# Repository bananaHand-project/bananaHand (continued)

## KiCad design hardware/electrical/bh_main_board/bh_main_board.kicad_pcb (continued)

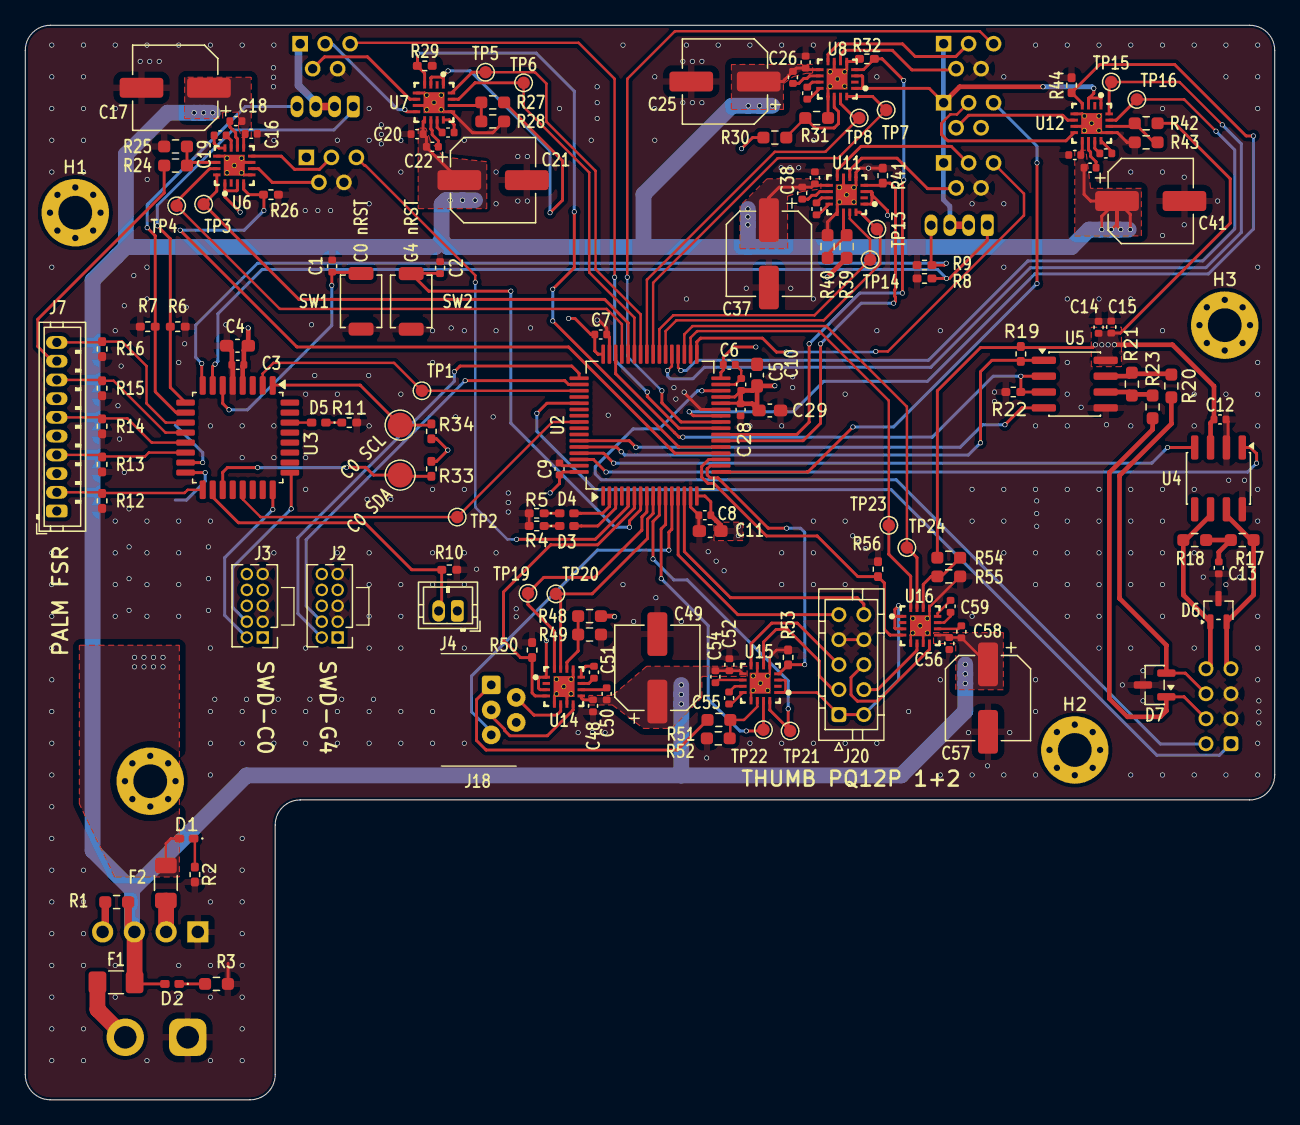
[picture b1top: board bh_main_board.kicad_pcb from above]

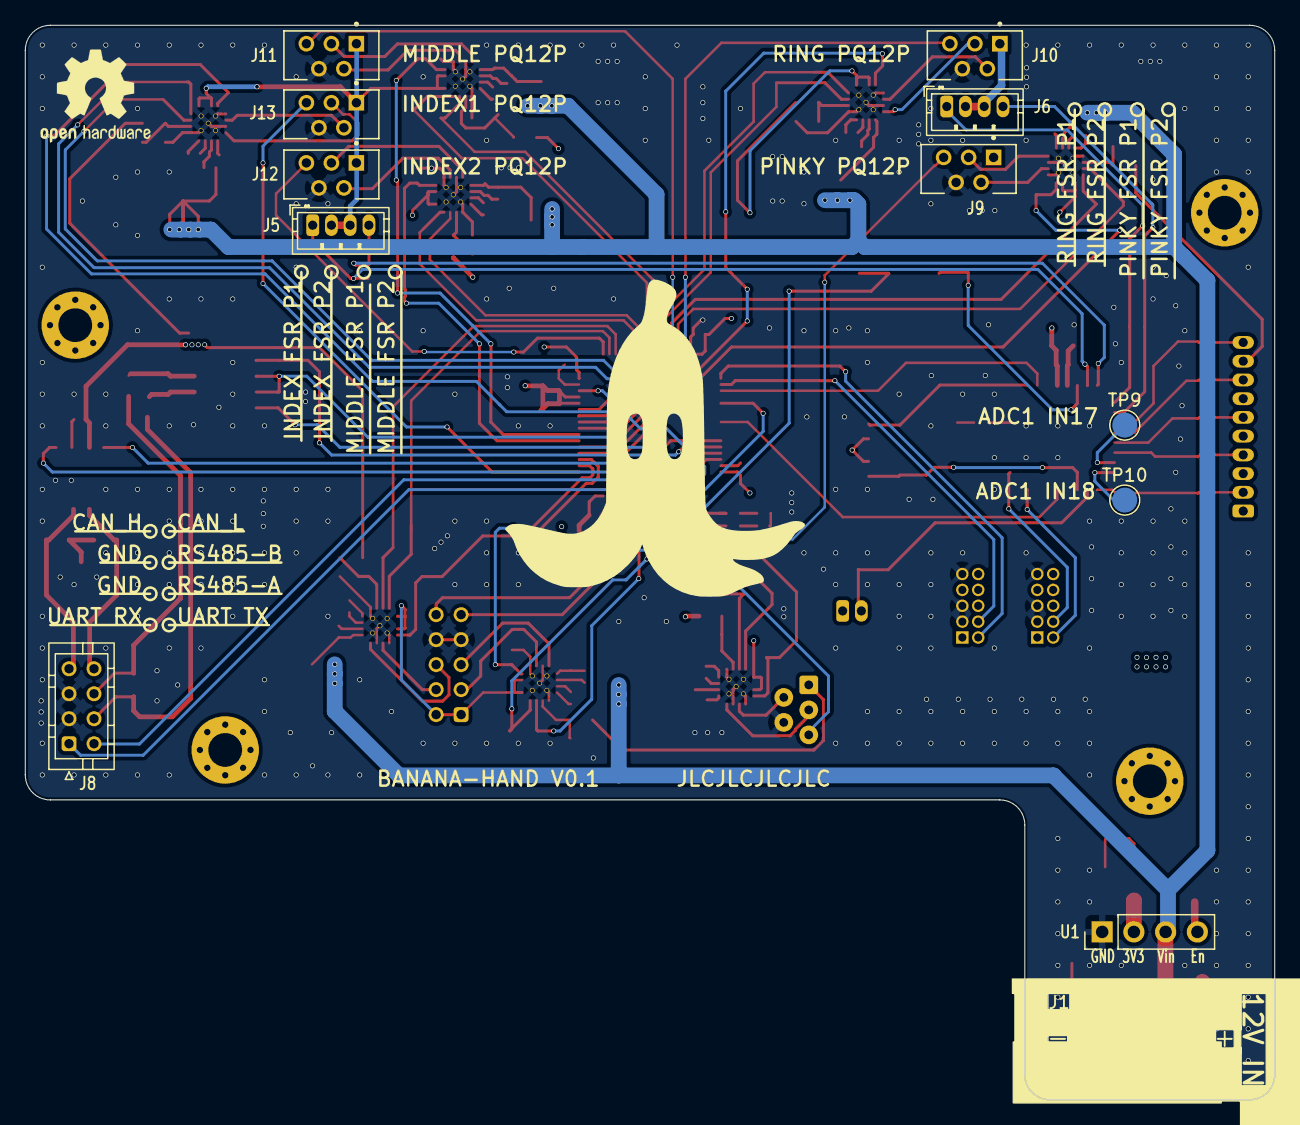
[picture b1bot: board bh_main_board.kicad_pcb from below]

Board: 4 copper layers, 100.0 x 86.0 mm, 163 parts (14 on the bottom side), 130 nets.

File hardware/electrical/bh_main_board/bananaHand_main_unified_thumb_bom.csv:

"Reference","Qty","Value","DNP","Exclude from BOM","Exclude from Board","Footprint","Datasheet","MFR #","LCSC #"
"U6,U7,U8,U11,U12,U14,U15,U16","8","DRV8876GTR","","","","bananaHand:DRV8876GTR-MFG","https://www.ti.com/lit/ds/symlink/drv8876.pdf","DRV8876RGTR","C1852100"
"J18","1","HLW5R-2C7LF","","","","bananaHand:HLW5R-2C7LF","","HLW5R-2C7LF","C5406452"
"J9,J10,J11,J12,J13","5","HLW5S-2C7LF","","","","bananaHand:HLW5S-2C7LF","","HLW5S-2C7LF","C5406437"
"ART1","1","~","","Excluded from BOM","","bananaHand:mk_banana_footprint","","",""
"U1","1","MPM3610_3V3_Buck_Brkout","","","","bananaHand:MP3610_3V3_BUCK_BREAKOUT","https://github.com/adafruit/Adafruit-MPM3610-PCB","",""
"SW1,SW2","2","SW_Push","","","","Button_Switch_SMD:SW_SPST_TS-1088-xR025","~","TS-1088R-02526","C455281"
"C1,C2,C3,C6,C7,C8,C9,C12,C14,C15,C16,C18,C20,C22,C24,C26,C36,C38,C40,C42,C48,C50,C52,C54,C56,C58","26","100nF","","","","Capacitor_SMD:C_0402_1005Metric","~"," GRM155R71H104KE14D","C77020"
"C5","1","10nF","","","","Capacitor_SMD:C_0402_1005Metric","~"," GRM155R71H103KA88D","C77019"
"C13","1","4nF7","","","","Capacitor_SMD:C_0402_1005Metric","~","GRM1555C1H472JE01D","C1518204"
"C19,C23,C27,C39,C43,C51,C55,C59","8","22nF","","","","Capacitor_SMD:C_0402_1005Metric","~"," GRM155R71H223KA12D","C77023"
"C4,C11","2","4uF7","","","","Capacitor_SMD:C_0603_1608Metric_Pad1.08x0.95mm_HandSolder","~"," GRM188R6YA475KE15D","C162274"
"C10","1","1uF","","","","Capacitor_SMD:C_0603_1608Metric_Pad1.08x0.95mm_HandSolder","~","GCM188R71E105KA64D","C85862"
"C17,C21,C25,C37,C41,C57","6","47uF","","","","Capacitor_SMD:CP_Elec_6.3x5.8","~","EEEFP1V470AP","C401754"
"C49","1","100uF","","","","Capacitor_SMD:CP_Elec_6.3x5.8","~"," EEEFT1V101AP","C128464"
"J1","1","Conn_01x02_Pin","","","","Connector_AMASS:AMASS_XT30UPB-M_1x02_P5.0mm_Vertical","~","XT30UPB-M","C428721"
"J20","1","Conn_02x05_Odd_Even","","","","Connector_JST:JST_PHD_B10B-PHDSS_2x05_P2.00mm_Vertical","~","B10B-PHDSS(LF)(SN)","C471519"
"J8","1","Conn_02x04_Top_Bottom","","","","Connector_JST:JST_PHD_B8B-PHDSS_2x04_P2.00mm_Vertical","~","B8B-PHDSS(LF)(SN)","C157975"
"J7","1","Conn_01x10","","","","Connector_JST:JST_ZH_B10B-ZR_1x10_P1.50mm_Vertical","~","B10B-ZR(LF)(SN)","C158036"
"J4","1","Conn_01x02_Pad","","","","Connector_JST:JST_ZH_B2B-ZR_1x02_P1.50mm_Vertical","~","JST B2B-ZR(LF)(SN)","C158011"
"J5,J6","2","Conn_01x04_Pin","","","","Connector_JST:JST_ZH_B4B-ZR_1x04_P1.50mm_Vertical","~","JST B4B-ZR(LF)(SN)","C157997"
"J2,J3","2","Conn_02x05_Top_Bottom","","","","Connector_PinHeader_1.27mm:PinHeader_2x05_P1.27mm_Vertical","~","ZX-PZ1.27-2-5PZZ","C7501289"
"F2","1","750mA 36V","","","","Fuse:Fuse_1206_3216Metric","https://www.lcsc.com/datasheet/C49196638.pdf"," 1206L075/36NR","C49196638"
"F1","1","1A8 33V","","","","Fuse:Fuse_1206_3216Metric_Pad1.42x1.75mm_HandSolder","https://www.lcsc.com/datasheet/C49318377.pdf","YTL 1206L100/33V","C49318377"
"D1,D2,D3,D4,D5","5","LED","","","","LED_SMD:LED_0402_1005Metric_Pad0.77x0.64mm_HandSolder","~","XL-1005UYC","C25503856"
"H1,H2,H3","3","MountingHole","","Excluded from BOM","","MountingHole:MountingHole_2.5mm_Pad_Via","~","",""
"U3","1","STM32C071K8Tx","","","","Package_QFP:LQFP-32_7x7mm_P0.8mm","https://www.st.com/resource/en/datasheet/stm32c071k8.pdf","STM32C071K8T6","C43650208"
"U2","1","STM32G474RETx","","","","Package_QFP:LQFP-64_10x10mm_P0.5mm","https://www.st.com/resource/en/datasheet/stm32g474re.pdf","STM32G474RET6","C521608"
"U4","1","SN65HVD230DR","","","","Package_SO:SOIC-8_3.9x4.9mm_P1.27mm","http://www.ti.com/lit/ds/symlink/sn65hvd230.pdf","SN65HVD230DR","C12084"
"U5","1","SN65HVD1781","","","","Package_SO:SOIC-8_3.9x4.9mm_P1.27mm","https://www.ti.com/lit/ds/symlink/sn65hvd1781.pdf","SN65HVD1781DR","C42737"
"D7","1","SM712_SOT23","","","","Package_TO_SOT_SMD:SOT-23","https://www.littelfuse.com/~/media/electronics/datasheets/tv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","SM712-02HTG","C172881"
"D6","1","ESDCAN03-2BWY","","","","Package_TO_SOT_SMD:SOT-323_SC-70","https://www.st.com/en/protections-and-emi-filters/esdcan03-2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","ESDCAN03-2BWY","C1973833"
"R2,R4,R5,R11","4","100","","","","Resistor_SMD:R_0402_1005Metric_Pad0.72x0.64mm_HandSolder","~"," ERJ2RKF1000X","C413063"
"R6,R7,R8,R9,R10,R12,R13,R14,R15,R16,R19,R22","12","10k","","","","Resistor_SMD:R_0402_1005Metric_Pad0.72x0.64mm_HandSolder","~"," RT0402BRD0710KL","C190095"
"R26,R29,R32,R41,R44,R50,R53,R56","8","11k","","","","Resistor_SMD:R_0402_1005Metric_Pad0.72x0.64mm_HandSolder","~"," RT0402BRE0711KL","C705643"
"R33,R34","2","3300","","","","Resistor_SMD:R_0402_1005Metric_Pad0.72x0.64mm_HandSolder","~","RC0402FR-073K3L","C137992"
"R1","1","100k","DNP","","","Resistor_SMD:R_0603_1608Metric_Pad0.98x0.95mm_HandSolder","~"," RC0603FR-07100KL","C14675"
"R3","1","1200","","","","Resistor_SMD:R_0603_1608Metric_Pad0.98x0.95mm_HandSolder","~"," RC0603FR-071K2L","C114605"
"R17,R18","2","60","","","","Resistor_SMD:R_0603_1608Metric_Pad0.98x0.95mm_HandSolder","~","0603WAF604JT5E","C23090"
"R20,R23","2","10","","","","Resistor_SMD:R_0603_1608Metric_Pad0.98x0.95mm_HandSolder","~","RC0603FR-0710RL","C109318"
"R21","1","120","DNP","","","Resistor_SMD:R_0603_1608Metric_Pad0.98x0.95mm_HandSolder","~"," RC0603FR-07120RL","C114640"
"R24,R27,R30,R39,R42,R48,R51,R54","8","0","","","","Resistor_SMD:R_0603_1608Metric_Pad0.98x0.95mm_HandSolder","~","RC0603JR-070RL","C95177"
"R25,R28,R31,R40,R43,R49,R52,R55","8","0","DNP","","","Resistor_SMD:R_0603_1608Metric_Pad0.98x0.95mm_HandSolder","~","RC0603JR-070RL","C95177"
"ART2","1","Logo_Open_Hardware_Small","","Excluded from BOM","","Symbol:OSHW-Logo2_9.8x8mm_SilkScreen","~","",""
"TP1,TP2,TP3,TP4,TP5,TP6,TP7,TP8,TP13,TP14,TP15,TP16,TP19,TP20,TP21,TP22,TP23,TP24","18","TestPoint","","Excluded from BOM","","TestPoint:TestPoint_Pad_D1.0mm","~","",""
"TP9,TP10","2","TestPoint_Small","","Excluded from BOM","","TestPoint:TestPoint_Pad_D2.0mm","~","",""
"TP11,TP12","2","TestPoint_Small","","","","TestPoint:TestPoint_Pad_D2.0mm","~","",""

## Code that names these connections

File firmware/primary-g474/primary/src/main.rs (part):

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    let p = embassy_stm32::init(config);
    SHARED_CONTROL_MODE.write(DEFAULT_CONTROL_MODE.to_wire());

    // USART3: PC link (kept off PA2/PA3 because those are used as potentiometer inputs).
    let mut uart3_config = UartConfig::default();
    uart3_config.baudrate = TELEM_BAUD;
    let uart3 = Uart::new(
        p.USART3,
        p.PC11, // RX pin (PC -> MCU)
        p.PB10, // TX pin (MCU -> PC)
        Irqs,
        p.DMA1_CH6, // TX DMA channel
        p.DMA1_CH5, // RX DMA channel
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    let mut uart1_config = UartConfig::default();
    uart1_config.baudrate = FORCE_SENS_BAUD;

    // RX on PA15 from C0 USART1_TX (PB6).
    let uart1_rx = UartRx::new(p.USART2, Irqs, p.PA15, p.DMA1_CH1, uart1_config).unwrap();

    _spawner
        .spawn(c0_reader::c0_reader_task(uart1_rx, &SHARED_FORCE))
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    // ADC + position reader (G4 pots).
    let dma = p.DMA1_CH2;
    let adc = Adc::new(p.ADC1, AdcConfig::default());
    let pos_pins = position_adc_pins(p.PA0, p.PA1, p.PA2, p.PA3, p.PB0, p.PB1, p.PB11, p.PF0);
    _spawner
        .spawn(position_reader::position_reader_task(
            adc,
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    // ADC2 + current reader (same logical order as positions/commands).
    let current_dma = p.DMA2_CH1;
    let current_adc = Adc::new(p.ADC2, AdcConfig::default());
    let current_pins = current_adc_pins(p.PA4, p.PA5, p.PA6, p.PA7, p.PB2, p.PC4, p.PC5, p.PF1);
    _spawner
        .spawn(current_reader::current_reader_task(
            current_adc,
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    let period = period_reg_val(clocks(&p.RCC), APBPrescaler::DIV1, prescaler, PWM_FREQ).unwrap();

    // TIM1 pin/channel contract:
    // CH1=PC0 and CH2=PC1 drive thumb-revolve H-bridge.
    // CH3=PC2 and CH4=PC3 are kept enabled but currently unused.
    let thumb_revolve_ch1_pin = PwmPin::new(p.PC0, OutputType::PushPull); // TIM1_CH1
    let thumb_revolve_ch2_pin = PwmPin::new(p.PC1, OutputType::PushPull); // TIM1_CH2
    let thumb_flex_unused_ch1_pin = PwmPin::new(p.PC2, OutputType::PushPull); // TIM1_CH3 (unused)
    let thumb_flex_unused_ch2_pin = PwmPin::new(p.PC3, OutputType::PushPull); // TIM1_CH4 (unused)
    let thumb_pwm = SimplePwm::new(
        p.TIM1,
        Some(thumb_revolve_ch1_pin),
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
    // HRTIM channels mapped directly to actuators.
    let (ring, pinky, thumb_flex, index1, middle, index2_unused) = HrtimCore::new()
        .add_tim_a_ch1_ch2(p.PA8, p.PA9, period, prescaler)
        .add_tim_b_ch1_ch2(p.PA10, p.PA11, period, prescaler)
        .add_tim_c_ch1_ch2(p.PB12, p.PB13, period, prescaler)
        .add_tim_d_ch1_ch2(p.PB14, p.PB15, period, prescaler)
        .add_tim_e_ch1_ch2(p.PC8, p.PC9, period, prescaler)
        .add_tim_f_ch1_ch2(p.PC6, p.PC7, period, prescaler)
        .split_active()
        .unwrap();

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        index1,
        middle,
        index2_unused,
        thumb_pwm_ch.ch1, // TIM1_CH1 -> PC0 -> thumb_revolve_ch1
        thumb_pwm_ch.ch2, // TIM1_CH2 -> PC1 -> thumb_revolve_ch2
        thumb_pwm_ch.ch3, // TIM1_CH3 -> PC2 -> unused
        thumb_pwm_ch.ch4, // TIM1_CH4 -> PC3 -> unused
    );

    let mut controller = Controller::default();
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
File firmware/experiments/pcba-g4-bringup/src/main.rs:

#![no_std]
#![no_main]

mod fmt;

#[cfg(not(feature = "defmt"))]
use panic_halt as _;
#[cfg(feature = "defmt")]
use {defmt_rtt as _, panic_probe as _};

use core::{default, str};

use embassy_executor::{Spawner, task};
use embassy_stm32::mode::Async;
use embassy_stm32::usart::{Config as UartConfig, UartRx};
use embassy_stm32::{
    adc::{AdcChannel, AnyAdcChannel},
    gpio::{Level, Output, Speed},
    peripherals::{ADC1, ADC2},
};
use embassy_stm32::{bind_interrupts, gpio::OutputType, time::khz, timer::simple_pwm};
use embassy_time::{Duration, Timer};
use fmt::{Bytes, info};
use pq12p_actuator;

bind_interrupts!(struct Irqs {
    USART2 => embassy_stm32::usart::InterruptHandler<embassy_stm32::peripherals::USART2>;
});

#[task]
async fn uart_reader_task(mut rx: UartRx<'static, Async>) {
    let mut rx_buf = [0u8; 64];
    let mut line = [0u8; 64];
    let mut line_len = 0usize;

    loop {
        let n = match rx.read_until_idle(&mut rx_buf).await {
            Ok(n) => n,
            Err(_) => continue,
        };

        for &b in &rx_buf[..n] {
            if b == b'\n' {
                let msg = if line_len > 0 && line[line_len - 1] == b'\r' {
                    &line[..line_len - 1]
                } else {
                    &line[..line_len]
                };

                if let Ok(text) = str::from_utf8(msg) {
                    info!("G4 received: {}", text);
                } else {
                    info!("G4 received (bytes): {}", Bytes(msg));
                }

                line_len = 0;
                continue;
            }

            if line_len < line.len() {
                line[line_len] = b;
                line_len += 1;
            }
        }
    }
}

#[embassy_executor::main]
async fn main(spawner: Spawner) {
    let p = embassy_stm32::init(Default::default());
    let mut led1 = Output::new(p.PC13, Level::High, Speed::Low);
    let mut led2 = Output::new(p.PC14, Level::High, Speed::Low);

    let mut uart_config = UartConfig::default();
    uart_config.baudrate = 115_200;
    let uart_rx = UartRx::new(p.USART2, Irqs, p.PA15, p.DMA1_CH5, uart_config).unwrap();
    spawner.spawn(uart_reader_task(uart_rx)).unwrap();

    let ch3 = simple_pwm::PwmPin::new(p.PC8, OutputType::PushPull);
    let ch4 = simple_pwm::PwmPin::new(p.PC9, OutputType::PushPull);
    let mut pwm = simple_pwm::SimplePwm::new(
        p.TIM8,
        None,
        None,
        Some(ch3),
        Some(ch4),
        khz(20),
        Default::default(),
    );

    let mut pwm_channels = pwm.split();
    pwm_channels.ch3.enable();
    pwm_channels.ch4.enable();

    // pwm_channels.ch3.set_duty_cycle_fully_on();
    // pwm_channels.ch4.set_duty_cycle_percent(50);

    let pos_adc: AnyAdcChannel<'_, ADC1> = p.PB1.degrade_adc();
    let i_adc: AnyAdcChannel<'_, ADC2> = p.PC5.degrade_adc();

    let mut actuator =
        pq12p_actuator::Pq12P::new(pwm_channels.ch4, pwm_channels.ch3, pos_adc, i_adc);

    actuator.move_in(50);

    loop {
        led1.set_high();
        led2.set_low();
        Timer::after(Duration::from_millis(500)).await;
        led1.set_low();
        led2.set_high();
        Timer::after(Duration::from_millis(500)).await;
    }
}

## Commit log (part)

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2025-10-18 Inital embassy project commit.
2025-10-20 Working rough position control. Lots to improve on.
2025-11-11 add simple pretrained YOLO model to detect and classify household objects
2025-12-01 Init commit
2025-12-02 run logistic regression and SVM
2025-12-04 add updated MLP model
2025-12-04 Add MLP
2025-12-04 Add CNN
2025-12-04 updated CNN
2025-12-08 communication test with packets
2025-12-08 changed to now send and wait until receive for python script
2025-12-08 arduino code
2025-12-08 Added small delay after last move to position
2025-12-15 Enhance README with project description
    Added a description for the BananaHand project.
2025-12-21 Finished adding sensor reading methods. Requires hardware testing still.
2025-12-23 Added bang-bang position controller, removed old code, and fixed typos.
2025-12-30 Added move_to_pos to tests
2025-12-30 Added to test
2026-01-05 TIMA CH1 50%DC wokring with PAC
2026-01-06 Corrected comments and made PWM freq 20kHz
2026-01-07 Tested without motors working
2026-01-19 Got force sensor reading in c0 with rest of code
2026-01-19 force control finger
2026-01-20 param update
2026-01-23 fix uart test
2026-01-23 adding uart_test to firmware Cargo.toml
2026-01-23 how to add packages readme
2026-01-25 Started abstracting PAC code.
2026-01-26 Reogranized firmware file structure. Still needs to be tested.
2026-01-26 added caleb c071 adc code
2026-01-27 changing name of project pt 2
2026-01-27 Init vision based teleop ROS2 setup
2026-01-27 Create webcam node with live cam feed
2026-01-27 Create banana_interfaces package for custom messages
2026-01-27 use cobs framing and change from f401 to g474
2026-01-28 Working on all subtimers except F. I suspect there is an issue with the PAC.
2026-02-02 changed serial bridge node to use cobs framing
2026-02-02 more
2026-02-03 Got cobs working, g4 shared memory not working yet
2026-02-03 got shared memory working and cobs async sending/reading
2026-02-03 Got position reading shared memory working
2026-02-03 some testing with combined c0 and g4 telemetry comms code
2026-02-04 Init mediapipe hand tracking
2026-02-04 Saving progress before moving to new branch to work in new repo arch.
2026-02-04 Update READMEs
2026-02-05 Implemented better HAL for all subtimers in v2.
2026-02-11 Change thumb opposition calculation from thumb tip to index MCP to thumb tip to pinky MCP
2026-02-11 Added period register calculation function
2026-02-11 Add MediaPipe hand tracking (#7)
    * Init mediapipe hand tracking
    * Detect and publish hand landmarks
    * Convert hand landmarks to per-finger actuation commands
    * Update READMEs
    * Change thumb opposition calculation from thumb tip to index MCP to thumb tip to pinky MCP
2026-02-15 Blinky working on c0
2026-02-18 Added hrtim_pwm_lib, still need to test on hw
2026-02-18 Added inter-mcu uart test. Passed
2026-02-21 Improvments to simple pq12p actuator lib
2026-02-21 Testing motor driving circuit
2026-02-21 Made period calculator work with time::Hertz
2026-02-21 Changed period_reg_val to use Hertz type
2026-02-21 Updated main to match new period calc
2026-02-21 Added x32 in period calc and removed panics
2026-02-21 Fixed so pin deref is no longer necessary
2026-02-22 Fixed period calculator and made more clear
2026-02-22 Format line
2026-02-22 Fixed 100% duty cycle
2026-02-22 Add local crate for use of HRTIM1 as simple PWM channels. (#8)
    * Added hrtim_pwm_lib, still need to test on hw
    * Changed period_reg_val to use Hertz type
    * Updated main to match new period calc
    * Fixed warnings
    * Added x32 in period calc and removed panics
    * Fixed so pin deref is no longer necessary
2026-02-23 changing protocol to accmodate either type of message
2026-02-23 working telemetry sending
2026-02-23 experimental: Working Message Passing between C0 <-> G4 and G4<->PC (#9)
    * combine all g4 code into one experiment
    * some testing with combined c0 and g4 telemetry comms code
    * changing protocol to accmodate either type of message
    * working telemetry sending
    * updated ROS readme and removed redundant code
2026-03-01 Init commit grasp network
2026-03-01 Configure realsense camera and save images
2026-03-03 Got multi motor control working, check comments in uart_g4_combo main.rs for motor/pot mapping changes
2026-03-03 code cleanup, accounting for index 1 (silkscreen index 1) swapped channels
2026-03-03 minor change 1
2026-03-03 minor change 2
2026-03-03 minor change 3
2026-03-03 experimental: Multi Motor Position Control Working (#11)
    * changing protocol to accmodate either type of message
    * working telemetry sending
    * updated ROS readme and removed redundant code
    * Got multi motor control working, check comments in uart_g4_combo main.rs for motor/pot mapping changes
    * code cleanup, accounting for index 1 (silkscreen index 1) swapped channels
    * minor change 1
2026-03-05 connect from webcam tracking and then use a node to send from hand_traj to tx_positions
2026-03-05 update ros readme
2026-03-05 ROS: connect hand trajectory node to serial bridge (#12)
    * connect from webcam tracking and then use a node to send from hand_traj to tx_positions
    * update ros readme
2026-03-06 Added workspace Cargo.toml
2026-03-06 Add threading for webcam frame capture to reduce latency
    What changed:
    The main change is that _tick() no longer calls:
    ok, frame = self._cap.read()
    Instead, read() now happens in _capture_loop():
    ok, frame = self._cap.read()
    running continuously in a background thread. Then _tick() just publishes the most recent frame.
2026-03-06 Update comment
2026-03-06 Let codex cook
2026-03-06 Added workspace Cargo.toml (#13)
2026-03-06 GOT VISION BASED TELEOPERATION WORKING
2026-03-06 got force control working on PCB
2026-03-06 Preliminary testing, changed rb to k8
2026-03-06 got uart comm working (maybe) with kinova gen3)
2026-03-06 getting rid of global cargo.lock and cargo.toml, UNCOMMENTING C0 READER THREAD SPAWNING ON G4
2026-03-06 Revert "Add threading for webcam frame capture to reduce latency (#14)"
    This reverts commit a8b8891069f240c6f3db92f1195c75a104832268.
2026-03-07 Revert "Add threading for webcam frame capture to reduce latency (#14)" (#15)
    This reverts commit a8b8891069f240c6f3db92f1195c75a104832268.
2026-03-07 Removed Cargo.toml and .lock, too many issues
2026-03-08 fix alignment issues
2026-03-08 updating readme and fixing ctrl-c issue
2026-03-08 Removed Cargo.toml and .lock, too many issues (#16)
2026-03-08 Add FSR Visualizer Node with working fingertip heatmap functionality (#17)
    * first demo version - not tested with real FSR
    * fix alignment issues
    * updating readme and fixing ctrl-c issue
2026-03-09 fixed ordering of FSRs and added palm data for fsr visualizer
2026-03-10 Implemented triple phase calibration, improved thumb tracking, added support for thumb PWM timer, fixed joint pin mapping
2026-03-10 Added manual control node
2026-03-11 adding min/max motor position scaling for teleop
2026-03-12 Advisor Demo March 12 (#18)
    * Preliminary testing, changed rb to k8
    * got force control working on PCB
    * GOT VISION BASED TELEOPERATION WORKING
    * got uart comm working (maybe) with kinova gen3)
    * getting rid of global cargo.lock and cargo.toml, UNCOMMENTING C0 READER THREAD SPAWNING ON G4
    * fixed ordering of FSRs and added palm data for fsr visualizer
2026-03-13 Improve vision based teleop with dual cam support
2026-03-16 Realsense depth cam reconstruction
2026-03-17 Remove ground plane with RANSAC plane segmentation
2026-03-17 fsr visualizer updated
2026-03-17 Grasp classification
2026-03-17 Added edge case for 0% duty cycle
2026-03-17 Added edge case for 0% duty cycle (#21)
2026-03-18 Added common code space for force data between MCUs
2026-03-18 Wired in new force common code to primary and sensor fw
2026-03-18 Refactoring primary control code UNTESTED
2026-03-18 Created pos adc pin struct to clean old array
2026-03-18 Added from into for motor command types
2026-03-18 Removed swap logic in favour of simple comment
2026-03-18 Board config no longer needed
2026-03-18 mujoco sim initial test
2026-03-19 replaced with new hand design
2026-03-20 Added kicad models
2026-03-20 Added kicad files (#22)
2026-03-20 updating requirements.txt
2026-03-20 added ros-based switching between force and position control and also added teleop safe and regular modes
2026-03-20 added 3d mediapipe mapping
2026-03-20 DEFAULT MODE IS REGULAR MODE NOT SAFE MODE
2026-03-20 added current reading and publishing
2026-03-20 Started writing elec docs
2026-03-20 Add unified ROS visualization package with MuJoCo sim, FSR GUI, and new hand model (#23)
    * mujoco sim initial test
    * working mujoco visualizer with teleop, centralized visualization into one package
    * replaced with new hand design
    * updating requirements.txt
2026-03-20 Improve ground plane removal
2026-03-20 Improve grasp classification model
2026-03-20 Grasp classification model
2026-03-20 Create end to end scan to grasp pipeline
2026-03-20 Finished first draft of elec docs
2026-03-20 Linked to pcb sch
2026-03-20 Added known flaws section
2026-03-20 Removed random .lock file
2026-03-20 Add electrical content to repo (#25)
    * Added kicad models
    * Started writing elec docs
    * Finished first draft of elec docs
    * Linked to pcb sch
    * removed old images
    * Added known flaws section
2026-03-20 Grasp classification (#20)
    * Realsense depth cam reconstruction
    * Remove ground plane with RANSAC plane segmentation
    * Grasp classification model
    * Improve ground plane removal
    * Improve grasp classification model
    * Create end to end scan to grasp pipeline
2026-03-20 mujoco sim fixes
2026-03-20 foxglove heatmap extension
2026-03-20 got grasp execution working
2026-03-20 foxglove panel
2026-03-20 fixing typo
2026-03-20 Grasp Interpretation and Action (#26)
    * got grasp execution working
    * fixing typo
    ---------
2026-03-20 First draft of main readme
2026-03-20 Added demo gifs
2026-03-20 Try and synch gifs better
2026-03-20 Added logo banner
2026-03-20 Changed to usd
2026-03-20 First draft of main README (#28)
    * First draft of main readme
    * Added demo gifs
    * Try and synch gifs better
    * Added logo banner
    * Changed to usd
2026-03-20 Combined demo gif for synch
2026-03-20 Improve grasp classification
2026-03-20 updated hardware readme
    added link to CAD, BOM
2026-03-20 added new folder for assembly guide
2026-03-20 fixed header
2026-03-20 adding assembly guide
2026-03-20 changed folder name
2026-03-20 added assembly guide, resources folder, links to CAD and BOM (#31)
    * updated hardware readme
    added link to CAD, BOM
    * added new folder for assembly guide
    * Update README.md
    * fixed header
    * adding assembly guide
2026-03-20 Improve spherical vs cylindrical
2026-04-12 Added current reading task and tied into telemetry
2026-04-12 Added current reading task and tied into telem. Made sure to add all files lol
2026-04-12 Added control mode switching
2026-04-12 Fixde controller new to have default instead of using fixed gains
2026-04-15 added timeout retry logic for telem sender
2026-04-15 minor improvments to c071 code
2026-04-15 Returned to board map file style config.
2026-04-24 change no force command to coast
2026-04-24 added gate for sensing debug print statments
2026-04-24 moved force packet mapping to common
2026-04-27 Large FW refactor (#32)
    * Moved experiment in sensing and primary folders
    * Added common code space for force data between MCUs
    * Wired in new force common code to primary and sensor fw
    * Refactoring primary control code UNTESTED
    * Created pos adc pin struct to clean old array
    * Added from into for motor command types
2026-04-27 updated readme with more fw detail
